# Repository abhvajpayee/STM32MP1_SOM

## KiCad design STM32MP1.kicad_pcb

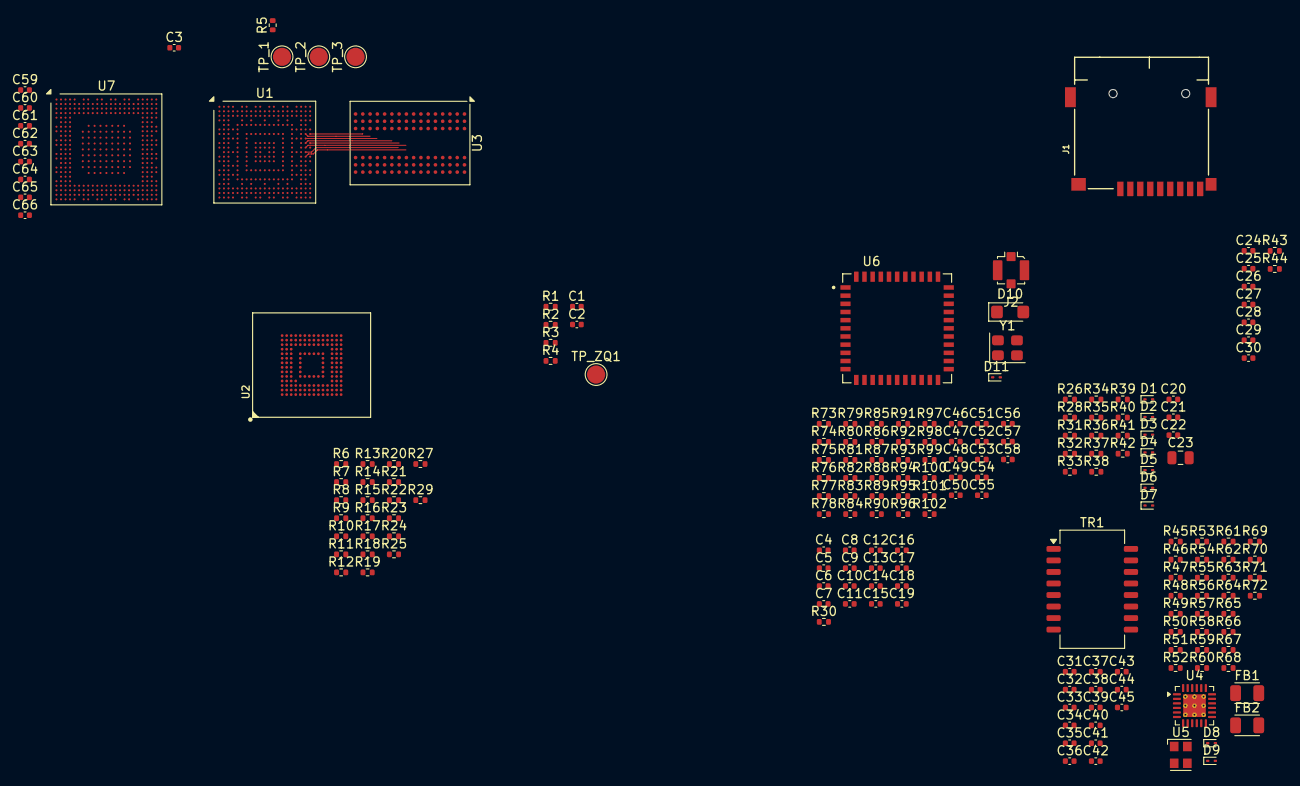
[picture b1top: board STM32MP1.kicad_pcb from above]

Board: 2 copper layers, 196 parts (0 on the bottom side), 154 nets.

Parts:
C1, C2, C3, C4, C5, C6, C10, C11, C12, C15, C16, C17, C21, C25, C26, C27, C28, C31, C33, C35, C42, C48, C49, C50, C52, C53, C55, C56, C57: 100nF; C_0402_1005Metric
C7, C8, C9, C13, C14, C18, C19, C20, C24, C30, C32, C34: 10uF; C_0402_1005Metric
C22: 2.7pF; C_0402_1005Metric
C23: 2.7pF; C_0805_2012Metric
C29: 2.2uF; C_0402_1005Metric
C36, C37, C38, C39, C58: 10pF; C_0402_1005Metric
C40, C41: 27pF; C_0402_1005Metric
C43: 470pF; C_0402_1005Metric
C44, C47, C51, C59, C60, C61, C62, C63, C64, C65, C66: 1uF; C_0402_1005Metric
C45: 22nf; C_0402_1005Metric
C46: 100uF; C_0402_1005Metric
C54: 4.7uF; C_0402_1005Metric
D1, D2, D3, D4, D5, D6, D7: ESD9B5.0ST5G; D_SOD-923
D8, D9, D11: ESD9B3.3ST5G; D_SOD-923
D10: SMF54A; D_SMF
FB1, FB2: FerriteBead_Small; L_Walsin_WLFM252009x
J1: Micro_SD_Card_Det1; J_SD_Card-micro_socket_A
J2: Conn_Coaxial_x2_Isolated; U.FL_Molex_MCRF_73412-0110_Vertical
R1, R5: 240R; R_0402_1005Metric
R2, R3, R6, R17, R18, R19, R20, R21, R22, R23, R24, R25, R29, R35, R36, R37, R38, R39, R40, R41, R48, R49, R50, R51, R52, R53, R54, R57, R75, R76, R77, R78, R79, R80, R89, R90, R100, R101: 10K; R_0402_1005Metric
R4, R67: 1.5K; R_0402_1005Metric
R7, R8, R9, R10, R11, R12, R13, R14, R15, R16, R26, R27, R28, R31, R32, R33, R34, R58, R59, R60, R61, R62, R66: 33R; R_0402_1005Metric
R30: 100R; R_0402_1005Metric
R42, R43, R44, R45, R46, R47, R55, R56, R64, R65, R73, R74, R81, R82, R83, R84, R85, R86, R87, R88, R91, R92, R93, R94, R95, R96, R97, R98, R99, R102: 0R; R_0402_1005Metric
R63: 10R; R_0402_1005Metric
R68: 12.1K; R_0402_1005Metric
R69, R70, R71, R72: 49.9; R_0402_1005Metric
TP_1, TP_2, TP_3: TestPoint; TestPoint_Pad_D2.0mm
TP_ZQ1: TestPoint; TestPoint_Pad_D2.0mm
TR1: PT61017PEL; Transformer_Ethernet_Bourns_PT61017PEL
U1: STM32MP131DAFx; ST_TFBGA-320_11x11mm_Layout21x21_P0.5mm
U2: EMMC04G-S100-B08U; MICRON_EMMC_153-12
U3: AS4C256M16D3; BGA-96_9.0x13.0mm_Layout2x3x16_P0.8mm
U4: LAN8742A; VQFN-24-1EP_4x4mm_P0.5mm_EP2.5x2.5mm_ThermalVias
U5: KC2520Z; Oscillator_SMD_Kyocera_KC2520Z-4Pin_2.5x2.0mm
U6: FC905AAAMD; XCVR_FC905AAAMD
U7: STM32MP157DACx; ST_TFBGA-361_12x12mm_Layout23x23_P0.5mmP0.65mm
Y1: abr-asek-1-32768khz; Oscillator_SMD_Abracon_ASE-4Pin_3.2x2.5mm

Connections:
/DDR3_RAM/DDR_A0: U1.H20 (DDR_A0), U3.N3 (A0)
/DDR3_RAM/DDR_A1: U1.N21 (DDR_A1), U3.P7 (A1)
/DDR3_RAM/DDR_A2: U1.G20 (DDR_A2), U3.P3 (A2)
/DDR3_RAM/DDR_A3: U1.H19 (DDR_A3), U3.N2 (A3)
/DDR3_RAM/DDR_A4: U1.R19 (DDR_A4), U3.P8 (A4)
/DDR3_RAM/DDR_A5: U1.F20 (DDR_A5), U3.P2 (A5)
/DDR3_RAM/DDR_A6: U1.R21 (DDR_A6), U3.R8 (A6)
/DDR3_RAM/DDR_A7: U1.J17 (DDR_A7), U3.R2 (A7)
/DDR3_RAM/DDR_A8: U1.P19 (DDR_A8), U3.T8 (A8)
/DDR3_RAM/DDR_A9: U1.G21 (DDR_A9), U3.R3 (A9)
/DDR3_RAM/DDR_A10: U1.L18 (DDR_A10), U3.L7 (A10/AP)
/DDR3_RAM/DDR_A11: U1.N17 (DDR_A11), U3.R7 (A11)
/DDR3_RAM/DDR_A12: U1.M19 (DDR_A12), U3.N7 (A12/~BC)
/DDR3_RAM/DDR_A13: U1.G19 (DDR_A13), U3.T3 (A13)
/DDR3_RAM/DDR_A14: U1.N19 (DDR_A14), U3.T7 (A14)
/DDR3_RAM/DDR_BA0: U1.J19 (DDR_BA0), U3.M2 (BA0)
/DDR3_RAM/DDR_BA1: U1.P20 (DDR_BA1), U3.N8 (BA1)
/DDR3_RAM/DDR_BA2: U1.H18 (DDR_BA2), U3.M3 (BA2)
/DDR3_RAM/DDR_CTRL0: R30.1, U1.M20 (DDR_CLKP), U3.J7 (CK)
/DDR3_RAM/DDR_CTRL1: R30.2, U1.L20 (DDR_CLKN), U3.K7 (~CK)
/DDR3_RAM/DDR_CTRL2: R2.2, U1.N20 (DDR_CKE), U3.K9 (CKE)
/DDR3_RAM/DDR_CTRL3: U1.H17 (DDR_RESETN), U3.T2 (~RESET)
/DDR3_RAM/DDR_CTRL4: U1.J20 (DDR_CSN), U3.L2 (~CS)
/DDR3_RAM/DDR_CTRL5: U1.K20 (DDR_RASN), U3.J3 (~RAS)
/DDR3_RAM/DDR_CTRL6: U1.L19 (DDR_CASN), U3.K3 (~CAS)
/DDR3_RAM/DDR_CTRL7: U1.K19 (DDR_WEN), U3.L3 (~WE)
/DDR3_RAM/DDR_CTRL8: U1.J21 (DDR_ODT), U3.K1 (ODT)
/DDR3_RAM/DDR_CTRL9: U1.W21 (DDR_DQM1), U3.E7 (LDM)
/DDR3_RAM/DDR_CTRL10: U1.D21 (DDR_DQM0), U3.D3 (UDM)
/DDR3_RAM/DDR_CTRL11: U1.V20 (DDR_DQS1P), U3.F3 (LDQS)
/DDR3_RAM/DDR_CTRL12: U1.V21 (DDR_DQS1N), U3.G3 (~LDQS)
/DDR3_RAM/DDR_CTRL13: U1.C20 (DDR_DQS0P), U3.C7 (UDQS)
/DDR3_RAM/DDR_CTRL14: U1.C21 (DDR_DQS0N), U3.B7 (~UDQS)
/DDR3_RAM/DDR_DQ0: U1.B21 (DDR_DQ0), U3.E3 (DQ0)
/DDR3_RAM/DDR_DQ1: U1.B20 (DDR_DQ1), U3.F7 (DQ1)
/DDR3_RAM/DDR_DQ2: U1.D19 (DDR_DQ2), U3.F2 (DQ2)
/DDR3_RAM/DDR_DQ3: U1.E19 (DDR_DQ3), U3.F8 (DQ3)
/DDR3_RAM/DDR_DQ4: U1.B19 (DDR_DQ4), U3.H3 (DQ4)
/DDR3_RAM/DDR_DQ5: U1.D20 (DDR_DQ5), U3.H8 (DQ5)
/DDR3_RAM/DDR_DQ6: U1.E20 (DDR_DQ6), U3.G2 (DQ6)
/DDR3_RAM/DDR_DQ7: U1.F19 (DDR_DQ7), U3.H7 (DQ7)
/DDR3_RAM/DDR_DQ8: U1.T20 (DDR_DQ8), U3.D7 (DQ8)
/DDR3_RAM/DDR_DQ9: U1.U20 (DDR_DQ9), U3.C3 (DQ9)
/DDR3_RAM/DDR_DQ10: U1.T19 (DDR_DQ10), U3.C8 (DQ10)
/DDR3_RAM/DDR_DQ11: U1.W20 (DDR_DQ11), U3.C2 (DQ11)
/DDR3_RAM/DDR_DQ12: U1.W19 (DDR_DQ12), U3.A7 (DQ12)
/DDR3_RAM/DDR_DQ13: U1.U19 (DDR_DQ13), U3.A2 (DQ13)
/DDR3_RAM/DDR_DQ14: U1.Y21 (DDR_DQ14), U3.B8 (DQ14)
/DDR3_RAM/DDR_DQ15: U1.Y20 (DDR_DQ15), U3.A3 (DQ15)
/DDR3_RAM/GND: C1.2, C2.2, C3.2, C4.2, C5.2, C6.2, C7.2, C8.2, C9.2, C10.2, C11.2, C12.2, C13.2, C14.2, C15.2, C16.2, C17.2, C18.2, C19.2, C59.1, C60.1, C61.1, C62.1, C63.1, C64.1, C65.1, C66.1, R1.2, R2.1, R3.1, R5.2, U1.A1 (VSS), U1.A21 (VSS), U1.AA1 (VSS), U1.AA18 (VSS_PLL2), U1.AA21 (VSS), U1.B12 (VSS), U1.D16 (VSS), U1.E5 (VSS), U1.E6 (VSS), U1.E11 (VSS), U1.E16 (VSS), U1.F5 (VSS), U1.F17 (VSS), U1.F18 (VSS), U1.F21 (VSS), U1.G8 (VSS), U1.G12 (VSS), U1.G14 (VSS), U1.H7 (VSS), U1.H15 (VSS), U1.J10 (VSS), U1.J12 (VSS), U1.K1 (VSS_PLL), U1.K9 (VSS), U1.K10 (VSS), U1.K11 (VSS), U1.K12 (VSS), U1.K13 (VSS), U1.K21 (VSS), U1.L5 (VSS), U1.L10 (VSS), U1.L12 (VSS), U1.L15 (VSS), U1.L17 (VSS), U1.M1 (VSS), U1.M7 (VSS), U1.M9 (VSS), U1.M10 (VSS), U1.M11 (VSS), U1.M12 (VSS), U1.M13 (VSS), U1.N11 (VSS), U1.P7 (VSS), U1.P15 (VSS), U1.R8 (VSS), U1.R11 (VSS), U1.R14 (VSS), U1.T1 (VSS), U1.T5 (VSS), U1.T17 (VSS), U1.T21 (VSS), U1.U3 (VSS_ANA), U1.U5 (VSS), U1.U6 (VSS), U1.U9 (VSSA), U1.U11 (VSS), U1.U13 (VSS), U1.U16 (VSS), U1.V16 (VSS), U1.W16 (VSS), U1.Y14 (VSS_USBHS), U3.A9 (VSS), U3.B1 (VSSQ), U3.B3 (VSS), U3.B9 (VSSQ), U3.D1 (VSSQ), U3.D8 (VSSQ), U3.E1 (VSS), U3.E2 (VSSQ), U3.E8 (VSSQ), U3.F9 (VSSQ), U3.G1 (VSSQ), U3.G8 (VSS), U3.G9 (VSSQ), U3.J2 (VSS), U3.J8 (VSS), U3.M1 (VSS), U3.M9 (VSS), U3.P1 (VSS), U3.P9 (VSS), U3.T1 (VSS), U3.T9 (VSS)
/DDR3_RAM/RESET_N: R3.2, R4.2
/DDR3_RAM/ZQ: R1.1, TP_ZQ1.1, U3.L8 (ZQ)
/EMMC/EMMC0: R7.1, U1.B16 (PB14)
/EMMC/EMMC1: R8.1, U1.B15
/EMMC/EMMC2: R9.1, U1.C14 (PB3)
/EMMC/EMMC3: R10.1, U1.C16 (PB4)
/EMMC/EMMC4: R11.1, U1.A16 (PF0)
/EMMC/EMMC5: R12.1, U1.A15 (PB9)
/EMMC/EMMC6: R13.1, U1.B14 (PC6)
/EMMC/EMMC7: R14.1, U1.C13 (PC7)
/EMMC/EMMC8: R15.1, U1.C17 (PG6)
/EMMC/EMMC9: R16.1, U1.B17 (PE3)
/EMMC/EMMC10: R27.1, U1.Y11 (NRST)
/EMMC/EMMC_3V3: C24.1, C25.1, C26.1, C27.1, C28.1, R6.2, R17.2, R18.2, R19.2, R20.2, R21.1, R22.1, R23.1, R24.1, R25.1, R29.1, R43.1, R44.1, U2.C6 (VCCQ1), U2.E6 (VCC1), U2.F5 (VCC2), U2.J10 (VCC3), U2.K9 (VCC4), U2.M4 (VCCQ2), U2.N4 (VCCQ3), U2.P3 (VCCQ4), U2.P5 (VCCQ5)
/EMMC/EMMC_CLK: C30.1, R16.2, R25.2, U2.M6 (CLK)
/EMMC/EMMC_CMD: R15.2, R24.2, U2.M5 (CMD)
/EMMC/EMMC_DATA0: R6.1, R7.2, U2.A3 (DAT0)
/EMMC/EMMC_DATA1: R8.2, R17.1, U2.A4 (DAT1)
/EMMC/EMMC_DATA2: R9.2, R18.1, U2.A5 (DAT2)
/EMMC/EMMC_DATA3: R10.2, R19.1, U2.B2 (DAT3)
/EMMC/EMMC_DATA4: R11.2, R20.1, U2.B3 (DAT4)
/EMMC/EMMC_DATA5: R12.2, R21.2, U2.B4 (DAT5)
/EMMC/EMMC_DATA6: R13.2, R22.2, U2.B5 (DAT6)
/EMMC/EMMC_DATA7: R14.2, R23.2, U2.B6 (DAT7)
/EMMC/GND: C24.2, C25.2, C26.2, C27.2, C28.2, C29.2, C30.2, U2.A6 (VSS1), U2.A7 (RFU@1), U2.C4 (VSSQ1), U2.E7 (VSS2), U2.G5 (VSS3), U2.H10 (VSS4), U2.J5 (VSS5), U2.K8 (VSS6), U2.N2 (VSSQ2), U2.N5 (VSSQ3), U2.P4 (VSSQ4), U2.P6 (VSSQ5)
/EMMC/~SYS_RST: R27.2, R29.2, U2.K5 (RST#)
/Ethernet/AVDD: FB1.1, FB2.2, R69.1, R70.1, R71.1, R72.1, U4.1 (VDD2A), U4.19 (VDD1A)
/Ethernet/ETH1_SPEED: R55.2, R56.2, R57.2, U4.2 (LED2/~INTSEL)
/Ethernet/GND: C31.2, C32.2, C33.2, C34.2, C35.2, C36.2, C37.2, C38.2, C39.2, C40.2, C41.2, C42.2, C43.2, C44.2, C45.2, R54.1, R57.1, R68.2, U4.25 (VSS), U5.2 (GND), U5.4 (VCC)
/Ethernet/RMII0: R58.1, U1.AA9 (PG13)
/Ethernet/RMII1: R59.1, U1.Y10 (PG14)
/Ethernet/RMII2: R60.1, U1.AA2 (PB11)
/Ethernet/RMII3: R61.1, U1.Y7 (PC4)
/Ethernet/RMII4: R62.1, U1.AA7 (PC5)
/Ethernet/RMII6: R64.1, U1.Y4 (PA2)
/Ethernet/RMII7: R65.1, U1.V3 (PG2)
/Ethernet/SYS_3V3: C32.1, C33.1, C34.1, C35.1, C42.1, FB2.1, R48.2, R49.2, R50.2, R51.2, R52.2, R53.2, R67.2, U4.9 (VDDIO)
/Ethernet/VDDCR: C43.1, C44.1, U4.6 (VDDCR)
/Ethernet/XTAL1: C41.1, U4.5 (XTAL1/CLKIN), U5.3 (CLK)
/Ethernet/XTAL2: R45.1, U4.4 (XTAL2)
/SD_CARD/GND: C20.2, C21.2, C22.2, C23.2, D1.1 (A1), D2.1 (A1), D3.1 (A1), D4.1 (A1), D5.1 (A1), D6.1 (A1), D7.1 (A1), J1.6 (VSS)
/SD_CARD/uSD_BUS5: C23.1, D4.2 (A2), J1.5 (CLK), R38.2
/SD_CARD/uSD_BUS6: C22.1, R34.2
/STM32MP1_Processor/VDD_CORE: C59.2, C60.2, C61.2, C62.2, C63.2, C64.2, C65.2, C66.2, U1.G11 (VDDCORE), U1.J11 (VDDCORE), U1.J15 (VDDCORE), U1.L7 (VDDCORE), U1.L9 (VDDCORE), U1.L13 (VDDCORE), U1.N10 (VDDCORE), U1.N13 (VDDCORE), U1.N15 (VDDCORE), U1.R10 (VDDCORE), U1.R13 (VDDCORE), U1.U12 (VDDCORE), U1.U14 (VDDCORE)
/STM32MP1_Processor/VDD_CPU: U1.E7 (VDDCPU), U1.E10 (VDDCPU), U1.G5 (VDDCPU), U1.G7 (VDDCPU), U1.G10 (VDDCPU), U1.K5 (VDDCPU), U1.K7 (VDDCPU)
/STM32MP1_Processor/VDD_DDR: C1.1, C2.1, C3.1, C4.1, C5.1, C6.1, C7.1, C8.1, C9.1, C10.1, C11.1, C12.1, C13.1, C14.1, C15.1, C16.1, C17.1, C18.1, C19.1, R4.1, U1.E15 (VDDQ_DDR), U1.G15 (VDDQ_DDR), U1.G17 (VDDQ_DDR), U1.K15 (VDDQ_DDR), U1.K17 (VDDQ_DDR), U1.M15 (VDDQ_DDR), U1.M17 (VDDQ_DDR), U1.R15 (VDDQ_DDR), U1.R17 (VDDQ_DDR), U1.T18 (DDR_VREF), U1.U15 (VDDQ_DDR), U3.A1 (VDDQ), U3.A8 (VDDQ), U3.B2 (VDD), U3.C1 (VDDQ), U3.C9 (VDDQ), U3.D2 (VDDQ), U3.D9 (VDD), U3.E9 (VDDQ), U3.F1 (VDDQ), U3.G7 (VDD), U3.H1 (VREFDQ), U3.H2 (VDDQ), U3.H9 (VDDQ), U3.K2 (VDD), U3.K8 (VDD), U3.M8 (VREFCA), U3.N1 (VDD), U3.N9 (VDD), U3.R1 (VDD), U3.R9 (VDD)
/STM32MP1_Processor/VDD_USB_3V3: U1.E12 (VDD), U1.G9 (VDD), U1.G13 (VDD), U1.J7 (VDD), U1.J9 (VDD), U1.J13 (VDD), U1.M5 (VDD), U1.N7 (VDD), U1.N9 (VDD), U1.N12 (VDD), U1.R5 (VDD), U1.R7 (VDD), U1.R9 (VDD), U1.R12 (VDD), U1.U7 (VDD), U1.W11 (VDD)
/STM32MP1_Processor/ZQ: R5.1, TP_2.1, U1.R20 (DDR_ZQ)
/Wifi/GND: C46.2, C47.2, C48.2, C49.2, C50.2, C51.2, C52.2, C53.2, C54.2, C55.2, C56.2, C57.2, D10.2 (A2), D11.1 (A1), J2.2 (Ext1), U6.1 (GND), U6.3 (GND__1), U6.20 (GND__2), U6.31 (GND__3), U6.33 (GND__4), U6.36 (GND__5), Y1.2 (GND)
/Wifi/SYS_3V3: D10.1 (A1), R73.2, R74.2, R75.2, R76.2, R77.2, R78.2, R79.2, R80.2, R89.2, R90.2, R100.1, R101.1
unnamed: C57.1, C58.2, R102.2
unnamed: D1.2 (A2), J1.1 (DAT2), R26.1, R35.2
unnamed: D2.2 (A2), J1.2 (DAT3/CD), R28.1, R36.2
unnamed: D3.2 (A2), J1.3 (CMD), R31.1, R37.2
unnamed: D5.2 (A2), J1.7 (DAT0), R32.1, R39.2
unnamed: D6.2 (A2), J1.8 (DAT1), R33.1, R40.2
unnamed: D7.2 (A2), J1.9 (DET), R34.1, R41.2
unnamed: C39.1, D8.1 (A1), R69.2, TR1.3 (TD-), U4.22 (RXN)
unnamed: C38.1, D8.2 (A2), R70.2, TR1.1 (TD+), U4.23 (RXP)
unnamed: C37.1, D9.1 (A1), R71.2, TR1.8 (RD-), U4.20 (TXN)
unnamed: C36.1, D9.2 (A2), R72.2, TR1.6 (RD+), U4.21 (TXP)
unnamed: C56.1, D11.2 (A2), J2.1 (In1), R102.1
unnamed: C20.1, C21.1, J1.4 (VDD), R35.1, R36.1, R37.1, R38.1, R39.1, R40.1, R41.1, R42.1
unnamed: C45.1, FB1.2, TR1.2 (C_TD), TR1.7 (C_RD)
unnamed: TP_1.1, U1.P18 (DDR_ATO)
unnamed: TP_3.1, U1.P17 (DDR_DTO1)
unnamed: C29.1, U2.C2 (VDDI)
unnamed: R52.1, R63.2, U4.11 (CRS_DV/MODE2)
unnamed: R65.2, U4.13 (MDC)
unnamed: R64.2, R67.1, U4.12 (MDIO)
unnamed: R68.1, U4.24 (RBIAS)
unnamed: R49.1, R61.2, U4.8 (RXD0/MODE0)
unnamed: R50.1, R62.2, U4.7 (RXD1/MODE1)
unnamed: R51.1, R54.2, U4.10 (RXER/PHYAD0)
unnamed: R58.2, U4.17 (TXD0)
unnamed: R59.2, U4.18 (TXD1)
unnamed: R60.2, U4.16 (TXEN)
unnamed: R53.1, R66.2, U4.14 (~INT/REFCLKO)
unnamed: C31.1, R46.2, R47.2, R48.1, U4.15 (~RST)
unnamed: C40.1, R45.2, U5.1 (INH)
unnamed: C58.1, U6.2 (ANT_WIFI0/BT)
unnamed: R95.1, U6.44 (BT_CTS)
unnamed: R91.1, U6.34 (BT_EN)
unnamed: R92.1, U6.41 (BT_RTS)
unnamed: R94.1, U6.43 (BT_RXD)
unnamed: R93.1, U6.42 (BT_TXD)
unnamed: R99.1, R101.2, U6.7 (BT_WAKE_HOST)
unnamed: R98.1, R100.2, U6.6 (HOST_WAKE_BT)
unnamed: R75.1, R86.2, U6.17 (SDIO_CLK)
unnamed: R76.1, R85.2, U6.16 (SDIO_CMD)
unnamed: R80.1, R81.2, U6.18 (SDIO_DATA0)
unnamed: R79.1, R82.2, U6.19 (SDIO_DATA1)
unnamed: R78.1, R83.2, U6.14 (SDIO_DATA2)
unnamed: R77.1, R84.2, U6.15 (SDIO_DATA3)
unnamed: C46.1, C47.1, C48.1, C49.1, R73.1, U6.9 (VBAT)
unnamed: C54.1, U6.23 (VIN_LDO)
unnamed: C50.1, C51.1, C52.1, C53.1, R74.1, U6.22 (VIO)
unnamed: R87.2, R89.1, U6.12 (WLAN_EN)
unnamed: R96.1, U6.24 (WLAN_SLP_CLK)
unnamed: R88.2, R90.1, U6.13 (WLAN_WAKE)
unnamed: U7.1A3 (VSS), U7.1A5 (VSS), U7.1A7 (VSS), U7.1B2 (VSS), U7.1B4 (VSS), U7.1B6 (VSS), U7.1B8 (VSS), U7.1C1 (VSS), U7.1C3 (VSS), U7.1C5 (VSS), U7.1C7 (VSS), U7.1C9 (VSS), U7.1D2 (VSS), U7.1D4 (VSS), U7.1D6 (VSS), U7.1D8 (VSS), U7.1E1 (VSS), U7.1E3 (VSS), U7.1E5 (VSS), U7.1E7 (VSS), U7.1E9 (VSS), U7.1F2 (VSS), U7.1F4 (VSS), U7.1F6 (VSS), U7.1F8 (VSS), U7.1G3 (VSS), U7.1G5 (VSS), U7.1G7 (VSS), U7.1G9 (VSS), U7.1H4 (VSS), U7.1H6 (VSS), U7.1H8 (VSS), U7.1J3 (VSS), U7.1J5 (VSS), U7.1J7 (VSS), U7.A1 (VSS), U7.A23 (VSS), U7.AA5 (VSS), U7.AA8 (VSS), U7.AA12 (VSS), U7.AA21 (VSS), U7.AC1 (VSS), U7.AC23 (VSS), U7.C7 (VSS), U7.C12 (VSS), U7.C21 (VSS), U7.D4 (VSS), U7.F21 (VSS), U7.H3 (VSS), U7.K21 (VSS), U7.P3 (VSS), U7.P21 (VSS), U7.V21 (VSS), U7.W3 (VSS)
unnamed: R97.2, Y1.1 (EN)
unnamed: R96.2, Y1.3 (OUT)
unnamed: C55.1, R97.1, Y1.4 (Vdd)

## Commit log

2026-01-06 initial commit noting works yet
2026-01-22 Initial Connections
    Initial Draw
2026-01-22 added mmc schematic
2026-01-27 First
2026-01-27 Included Tushar's changed also added SDCARD module
2026-01-28 Completed ETH Module as per ref schematic also populated compatible busses in processor module
2026-01-30 Test
    Thanks
2026-01-30 Updated Processor With ETH Pins
    Also updated Capacitors and Resistors to 402
2026-01-31 Temporary changes
    My changes
2026-03-12 Added PMIC, WIFI and updated to STM32MP157 design
